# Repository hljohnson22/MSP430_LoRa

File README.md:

# MSP430_LoRa
This program is takes a temperature reading using one-wire commmunication, 
sends the reading to the LoRa board using SPI which transmits to the reciever, 
then goes into low power mode for 10 minutes.

Pin Outputs:<br />
p1.4 -> Temp sensor data line<br />
p5.2 -> Temp sensor power

p5.4 and p4.5 -> LoRa power in series
p1.5 (SCK)      -> LoRa SCK (ICSP pins)<br />
p1.6 (MISO/SOMI) -> LoRa MISO/SOMI (ICSP pins)<br />
p1.7 (MOSI/SIMO) -> LoRa MOSI/SIMO (ICSP pins)<br />
p5.1  -> LoRa D10 (chip select)<br />

Vcc = 3.3V

ICSP Pins:<br />
[]MISO | Vcc<br />
SCK | MOSI<br />
Reset | GND<br />

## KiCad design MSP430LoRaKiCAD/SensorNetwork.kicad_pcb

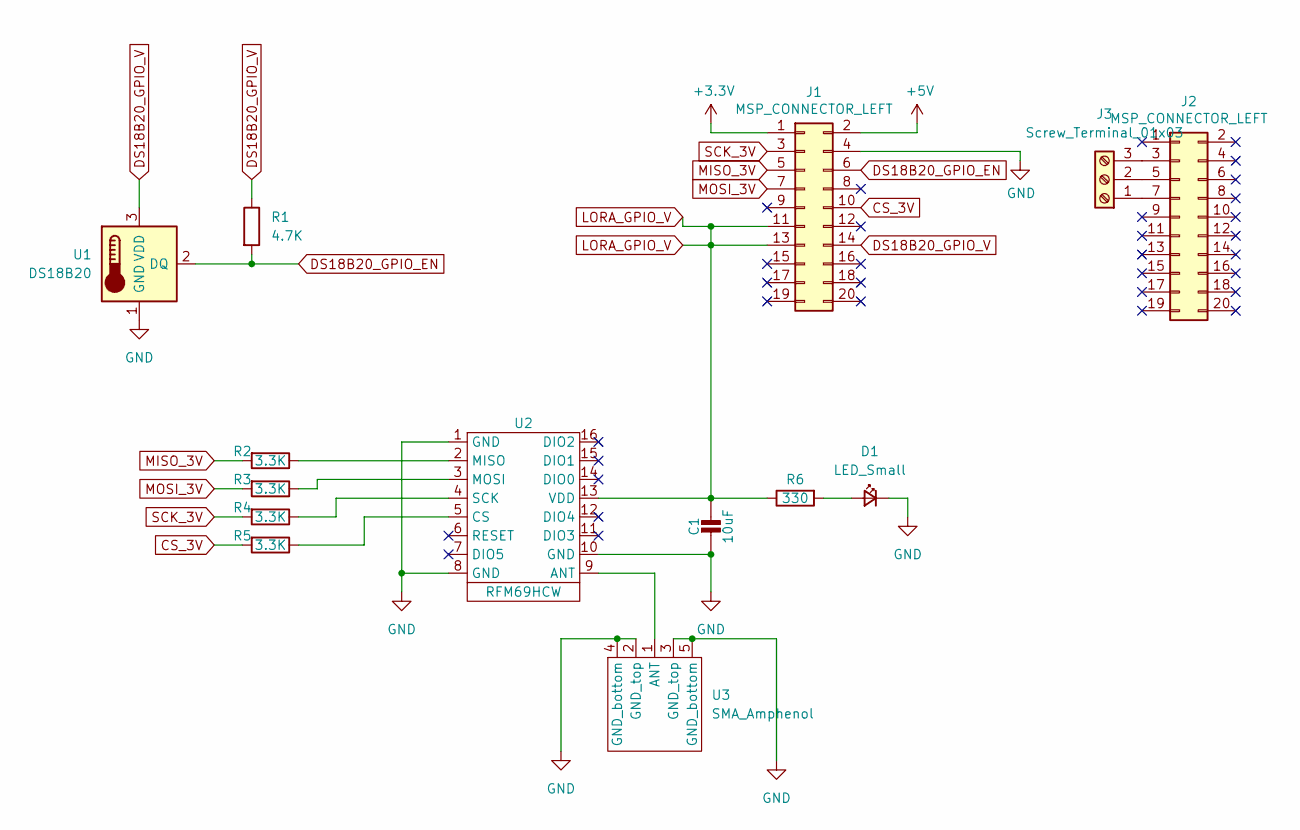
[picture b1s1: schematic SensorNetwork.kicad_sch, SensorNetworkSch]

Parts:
C1: 10uF; C_0805_2012Metric
D1: LED_Small; LED_0603_1608Metric
J1, J2: MSP_CONNECTOR_LEFT; PinHeader_2x10_P2.54mm_Vertical
J3: Screw_Terminal_01x03; PhoenixContact_MSTBVA_2,5_3-G-5,08_1x03_P5.08mm_Vertical
R1: 4.7K; R_0603_1608Metric
R2, R3, R4, R5: 3.3K; R_0603_1608Metric
R6: 330; R_0603_1608Metric
U1: DS18B20; TO-92_Inline
U2: RFM69HCW; LoRa_RFM
U3: SMA_Amphenol

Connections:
+3V3: J1.1
+5V: J1.2
CS_3V: J1.10, R5.2
DS18B20_GPIO_EN: J1.6, R1.2, U1.2 (DQ)
DS18B20_GPIO_V: J1.14, R1.1, U1.3 (VDD)
GND: C1.2, D1.1 (K), J1.4, U1.1 (GND), U2.1 (GND), U2.8 (GND), U2.10 (GND), U3.2 (GND_top), U3.3 (GND_top), U3.4 (GND_bottom), U3.5 (GND_bottom)
LORA_GPIO_V: C1.1, J1.11, J1.13, R6.1, U2.13 (VDD)
MISO_3V: J1.5, R2.2
MOSI_3V: J1.7, R3.2
unnamed: D1.2 (A), R6.2
unnamed: J2.3, J3.3
unnamed: J2.5, J3.2
unnamed: J2.7, J3.1
unnamed: R2.1, U2.2 (MISO)
unnamed: R3.1, U2.3 (MOSI)
unnamed: R4.1, U2.4 (SCK)
unnamed: R5.1, U2.5 (CS)
unnamed: U2.9 (ANT), U3.1 (ANT)
SCK_3V: J1.3, R4.2

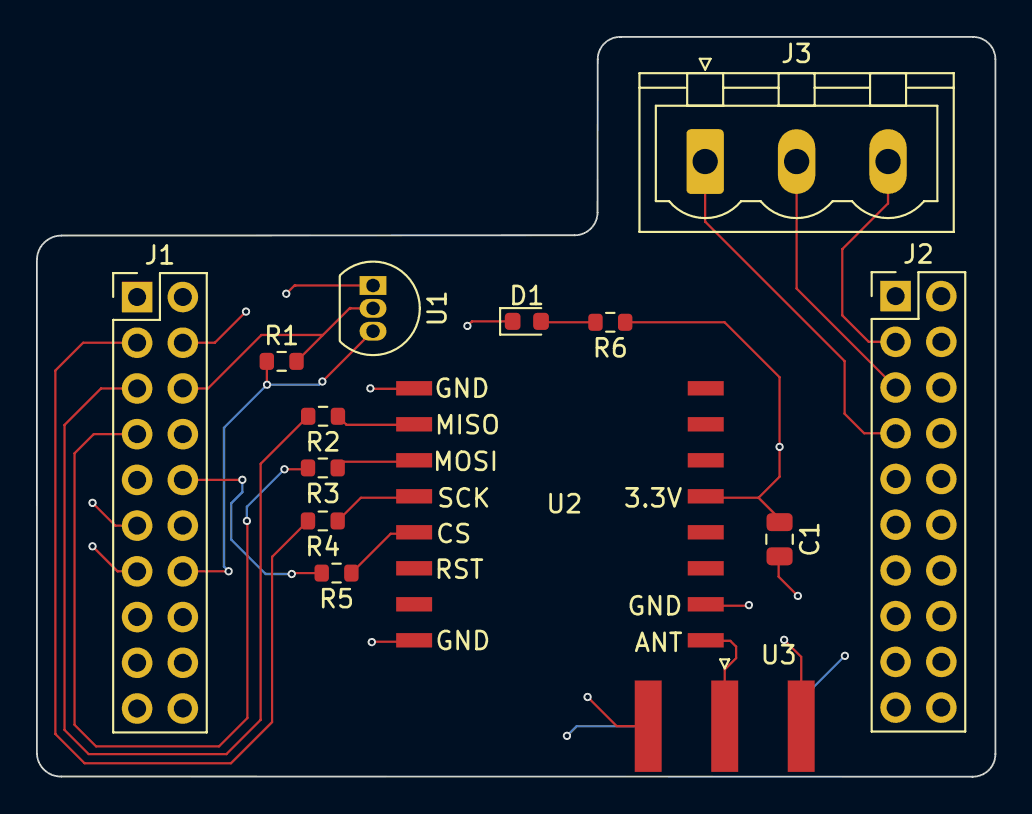
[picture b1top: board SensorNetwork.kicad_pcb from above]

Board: 4 copper layers, 53.3 x 41.1 mm, 14 parts (0 on the bottom side), 17 nets.

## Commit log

2022-04-18 Adding all files
    adding msp430 program files that reads sensor and sends data over lora.
2022-05-26 cleaning code
    Cleaning code and added documentation
2022-05-26 KiCAD files
    The files in the directory can be use to edit the boards, or create more.
2022-05-26 reorganizing
    Added arduino code
    reorganized repo.
